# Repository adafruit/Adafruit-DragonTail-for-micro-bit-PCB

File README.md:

## Adafruit DragonTail for micro:bit breadboard pin breakout PCB

<a href="http://www.adafruit.com/products/3695"><br/>
Click here to purchase one from the Adafruit shop</a>

PCB files for the Adafruit DragonTail for micro:bit. Format is EagleCAD schematic and board layout

For more details, check out the product page at
* https://www.adafruit.com/products/3695

### Description

The BBC micro:bit is a cute, all-in-one learning board, with LEDs, sensors, and even a Bluetooth LE radio built in. What it doesn't have is a set of 0.1" headers, for breadboard compatibility. Instead, there's a PCB 'card edge' connector that can slot into a matching socket. Now, if you want to hook up a servo, some NeoPixels, or some other simple component, you could use our alligator-to-header cables, and that will let you connect one or two parts to the power and P0, P1 or P2 pads. But...those alligator clips can slip around, and you don't get access to some of the more fun i/o pins, like I2C.

So, we made the Adafruit DragonTail for micro:bit. This breakout board has the card-edge connector for your micro:bit, and then breaks out all the pads so that it can be plugged in to any solderless breadboard. You even get two pads for the power railing! It comes fully assembled - no soldering required. And every pad is clearly labeled: by name, if it has an analog input, and when it is shared with the LED matrix.

### License

Adafruit invests time and resources providing this open source design, please support Adafruit and open-source hardware by purchasing products from [Adafruit](https://www.adafruit.com)!

Designed by Limor Fried/Ladyada for Adafruit Industries.

Creative Commons Attribution/Share-Alike, all text above must be included in any redistribution. See license.txt for additional details.

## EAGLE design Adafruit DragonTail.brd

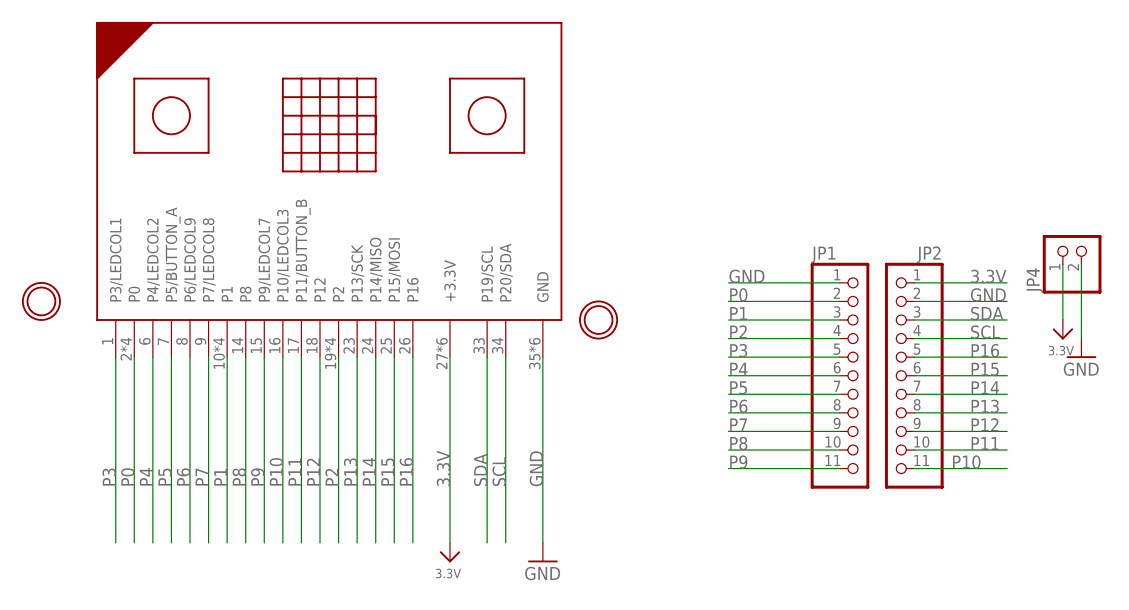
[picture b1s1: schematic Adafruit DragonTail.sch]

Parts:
JP1, JP2: HEADER-1X1176MIL; 1X11_ROUND_76
JP4: HEADER-1X2; 1X02_OVAL
MB1: MICRO:BIT_RA; 2X20_CARDEDGE_RA
U$9, U$10: MOUNTINGHOLE2.0; MOUNTINGHOLE_2.0_PLATED

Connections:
3.3V: JP2.1, JP4.1, MB1.27 (+3.3V), MB1.28 (+3.3V), MB1.29 (+3.3V), MB1.30 (+3.3V), MB1.31 (+3.3V), MB1.32 (+3.3V)
GND: JP1.1, JP2.2, JP4.2, MB1.35 (GND), MB1.36 (GND), MB1.37 (GND), MB1.38 (GND), MB1.39 (GND), MB1.40 (GND)
P0: JP1.2, MB1.2 (P0), MB1.3 (P0), MB1.4 (P0), MB1.5 (P0)
P1: JP1.3, MB1.10 (P1), MB1.11 (P1), MB1.12 (P1), MB1.13 (P1)
P2: JP1.4, MB1.19 (P2), MB1.20 (P2), MB1.21 (P2), MB1.22 (P2)
P3: JP1.5, MB1.1 (P3/LEDCOL1)
P4: JP1.6, MB1.6 (P4/LEDCOL2)
P5: JP1.7, MB1.7 (P5/BUTTON_A)
P6: JP1.8, MB1.8 (P6/LEDCOL9)
P7: JP1.9, MB1.9 (P7/LEDCOL8)
P8: JP1.10, MB1.14 (P8)
P9: JP1.11, MB1.15 (P9/LEDCOL7)
P10: JP2.11, MB1.16 (P10/LEDCOL3)
P11: JP2.10, MB1.17 (P11/BUTTON_B)
P12: JP2.9, MB1.18 (P12)
P13: JP2.8, MB1.23 (P13/SCK)
P14: JP2.7, MB1.24 (P14/MISO)
P15: JP2.6, MB1.25 (P15/MOSI)
P16: JP2.5, MB1.26 (P16)
SCL: JP2.4, MB1.33 (P19/SCL)
SDA: JP2.3, MB1.34 (P20/SDA)

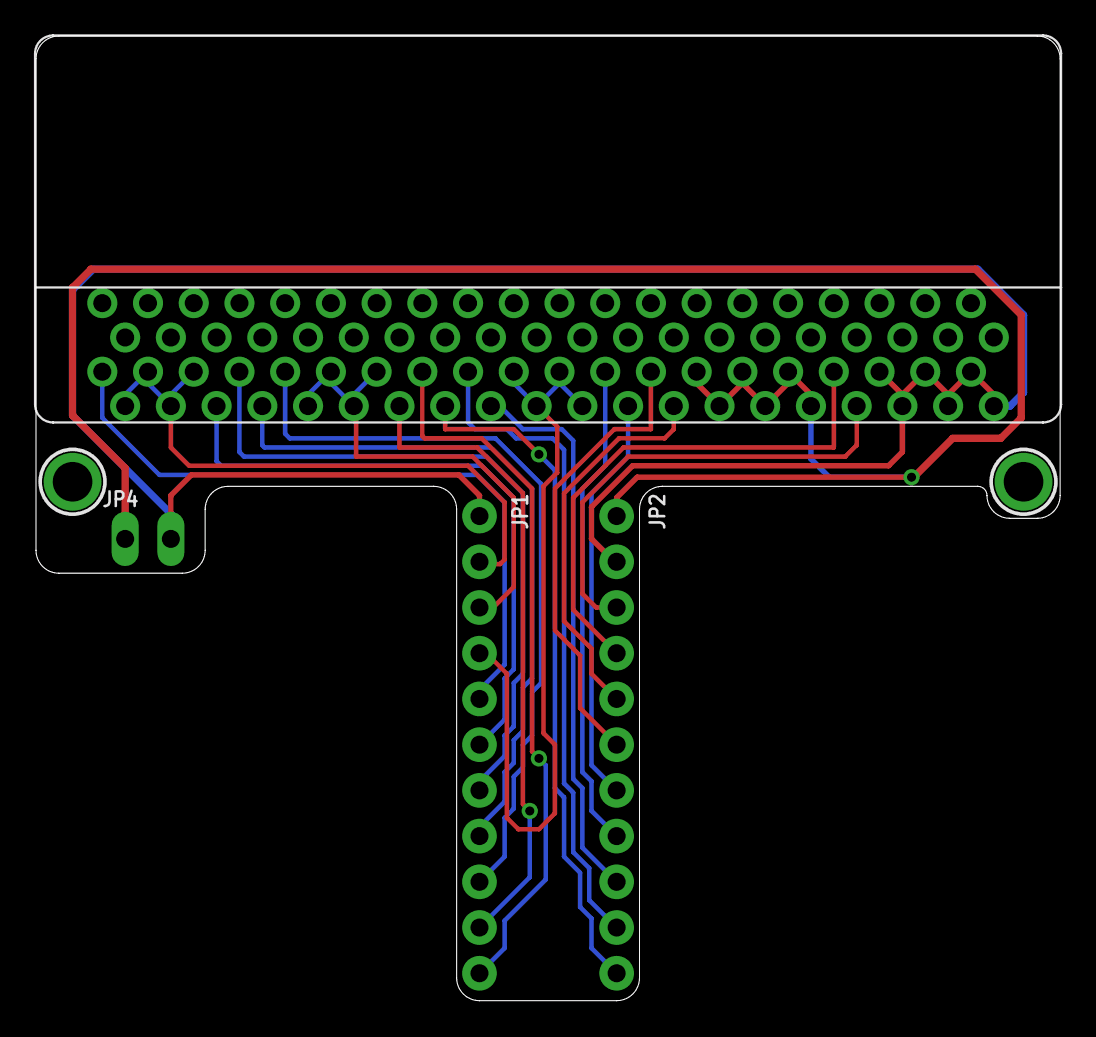
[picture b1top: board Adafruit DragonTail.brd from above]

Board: 2 copper layers, 56.9 x 53.6 mm, 8 parts (1 on the bottom side), 21 nets.

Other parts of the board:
U$3: TBREADBIT_BOT
U$6: TBREADBIT_TOP

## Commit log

2018-03-29 init

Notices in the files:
parts and their libraries:
microbuilder: This work is placed in the public domain, and may be freely used for commercial and non-commercial work with the following conditions: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
